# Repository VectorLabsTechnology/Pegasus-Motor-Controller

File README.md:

# Pegasus Motor Controller

## Objetivo

O objetivo do projeto é desenvolver um inversor para um motor síncrono de ímãs permanentes utilizando a técnica de controle orientado a campo. Com isso, se espera obter a familiaridadee com tecnologias modernas de controle de motores, tendo como objetivo final desenvolver um inversor capaz de acionar motores trifásicos e BLDC.

## Especificações

Em primeira instância, o motor a ser acionado será um motor oriundo de um _hoverboard_, brushless sensorado, operando a 48V e com potência máxima de 2,2kW. Com base nesses aprendizados, espera-se no futuro ser possível acionarmos um motor de maior tensão e potência, já de fabricação própria. As especificações técnicas mais específicas podem ser encontradas na [CT-001](/docs/CT-001-Especificacoes-Gerais.md).

## Organização do projeto

O repositório está dividido em quatro subdiretórios, `docs`, `fw`, `hw` e `sw`, que contêm respectivamente a documentação, firmware, hardware e software do projeto.
A parte de documentação é organizada majoritariamente no formato de [CTs](/docs/README.md). O design de hardware está sendo realizado com a ferramenta KiCad.

## Renders of the borads
Power Electronics:

Control Board:

Video of the test on a 3-phase induction motor

### Licença

O projeto está licenciado sob a licença MIT. Isso quer dizer que você tem o direto de reproduzir ele, tanto o software quanto o hardware.

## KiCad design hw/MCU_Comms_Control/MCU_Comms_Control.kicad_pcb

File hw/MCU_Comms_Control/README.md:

# Placa de controle

---

---

Essa placa é responsável por realizar o acionamento e controle dos motores. Utilizando um STM32F303, ela é capaz de medir a corrente ou força eletromotriz reversa de cada fase, possibilitando a comutação das bobinas. Além disso, possui entradas para sensores Hall, permitindo o uso de motores sensorados. 

Além do acionamento do motor, a placa realiza a comunicação com o resto do carro via barramento CAN, possibilitando o ajuste remoto de torque. Também possui uma entrada para o barramento de falha do carro, que desativa automaticamente a saída em caso de pane em qualquer um dos sistemas. Entradas para termistores permitem o monitoramento contínuo da temperatura da ponte do inversor, possibilitando o desarme em caso de sobreaquecimento. O monitoramento da tensão da bateria permite que as saídas sejam desligadas em caso de sobre/subtensão.

Com fim de telemetria, a placa conta com uma memória flash de 128Mbits, que pode ser lida através de conexão USB para possibilitar a caracterização da performance do inveersor e do motor, diagnosticar panes, entre outros.

---

Esse design é hardware livre e é disponibilizado através da licença CERN-OHL-S v2 (fortemente recíproca), disponível em inglês [aqui](https://ohwr.org/cern_ohl_s_v2.txt).

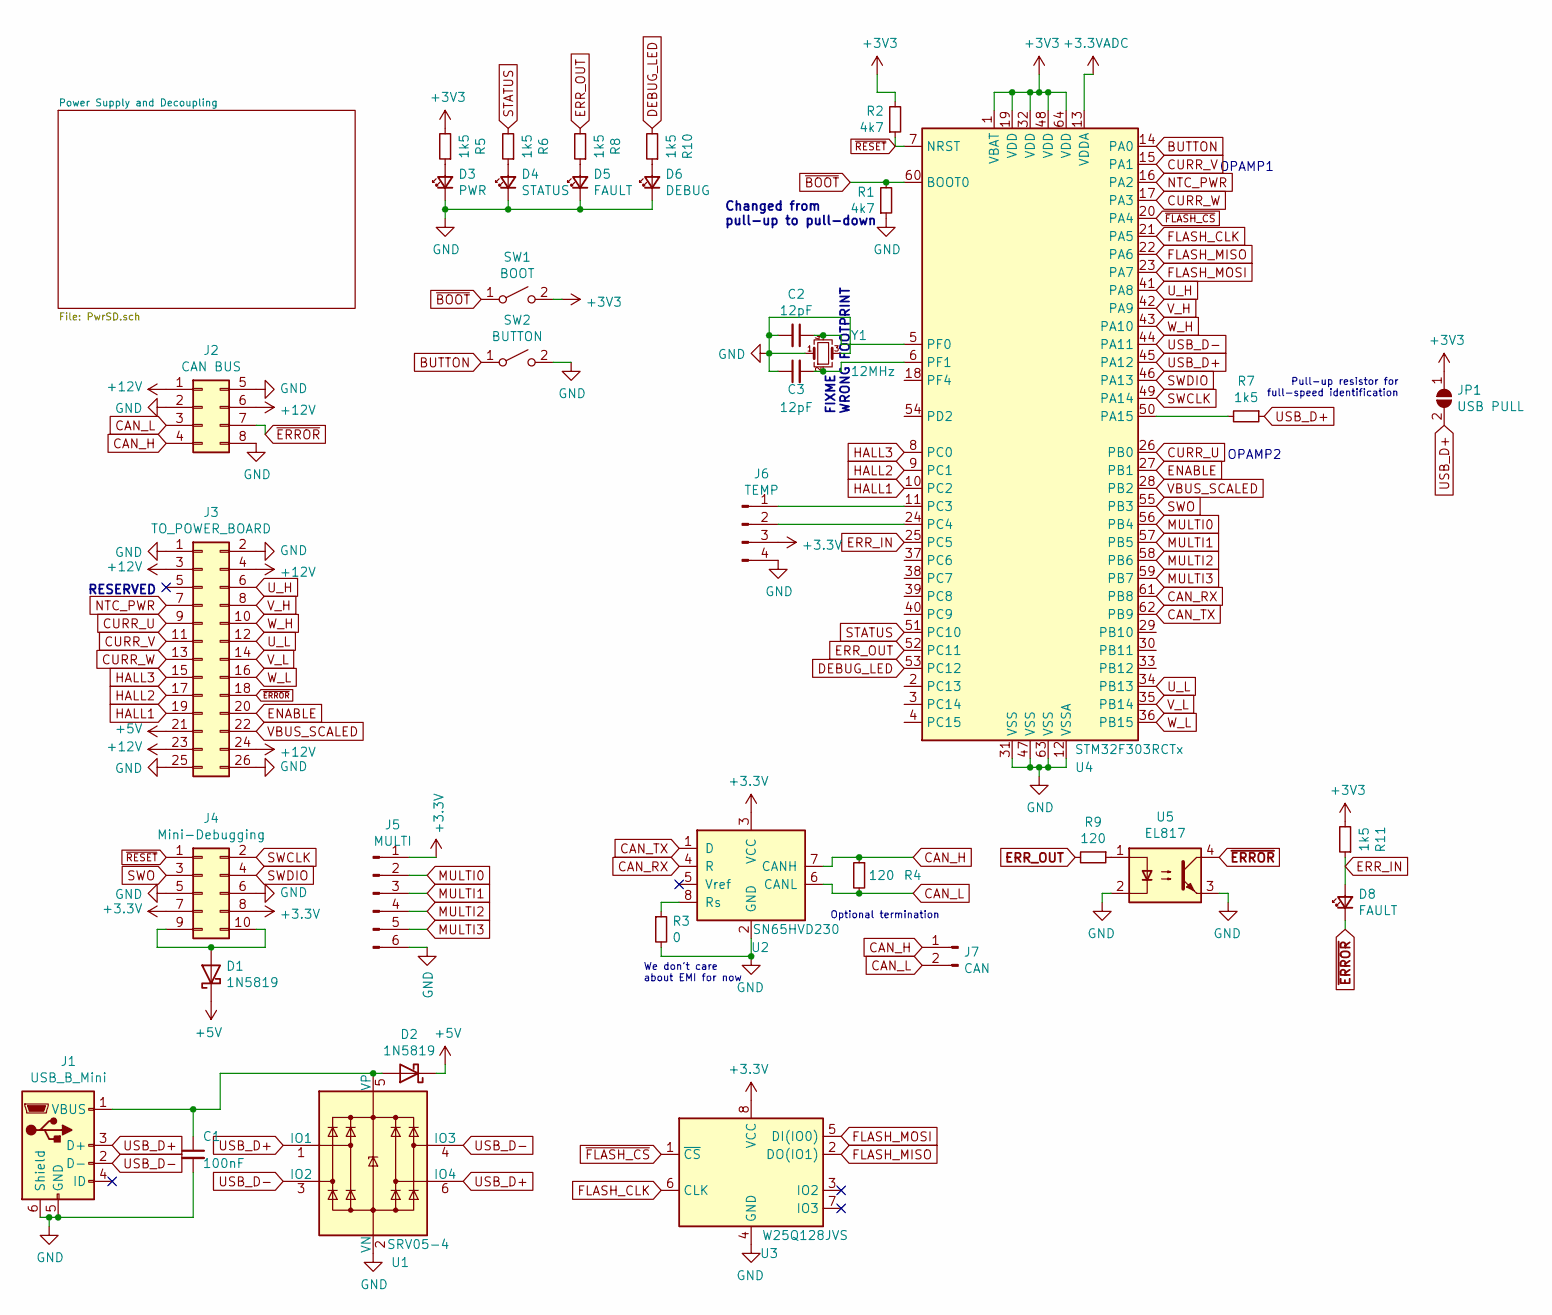
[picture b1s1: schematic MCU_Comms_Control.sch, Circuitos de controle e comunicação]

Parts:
C1: 100nF; C_0603_1608Metric; LCSC C14663
C2, C3: 12pF; C_0603_1608Metric; LCSC C38523
D1, D2: 1N5819; D_SOD-123; LCSC C8598
D3: PWR; LED_0603_1608Metric_Castellated; LCSC C72043
D4: STATUS; LED_0603_1608Metric_Castellated; LCSC C72041
D5, D8: FAULT; LED_0603_1608Metric_Castellated; LCSC C2286
D6: DEBUG; LED_0603_1608Metric_Castellated; LCSC C72041
J1: USB_B_Mini; USB_Micro-B_Molex-105133-0001
J2: CAN BUS; Molex_Mini-Fit_Jr_5566-08A_2x04_P4.20mm_Vertical
J3: TO_POWER_BOARD; IDC-Header_2x13_P2.54mm_Vertical
J4: Mini-Debugging; PinHeader_2x05_P2.54mm_Vertical
J5: MULTI; PinHeader_1x06_P2.54mm_Vertical
J6: TEMP; PinHeader_2x02_P2.54mm_Vertical
J7: CAN; PinHeader_1x02_P2.54mm_Vertical
JP1: USB PULL; SolderJumper-2_P1.3mm_Open_RoundedPad1.0x1.5mm
R1, R2: 4k7; R_0603_1608Metric; LCSC C23162
R3: 0; R_0603_1608Metric; LCSC C21189
R4, R9: 120; R_0805_2012Metric; LCSC C17437
R5, R6, R7, R8, R10, R11: 1k5; R_0603_1608Metric; LCSC C22843
SW1: BOOT; SW_SPST_PTS645
SW2: BUTTON; SW_SPST_PTS645
U1: SRV05-4; SOT-23-6; LCSC C85364
U2: SN65HVD230; SOIC-8_3.9x4.9mm_P1.27mm; LCSC C12084
U3: W25Q128JVS; SOIC-8_5.23x5.23mm_P1.27mm; LCSC C97521
U4: STM32F303RCTx; LQFP-64_10x10mm_P0.5mm
U5: EL817; SMDIP-4_W7.62mm; LCSC C106900
Y1: 12MHz; Crystal_SMD_3225-4Pin_3.2x2.5mm; LCSC C9002

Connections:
+3.3VADC: U4.13 (VDDA); also elsewhere on the board
+5V: D1.1 (K), D2.1 (K), J3.21; also elsewhere on the board
+12V: J2.1, J2.6, J3.3, J3.4, J3.23, J3.24; also elsewhere on the board
BUTTON: SW2.1 (A), U4.14 (PA0)
CAN_H: J2.4, J7.1, R4.1, U2.7 (CANH)
CAN_L: J2.3, J7.2, R4.2, U2.6 (CANL)
CAN_RX: U2.4 (R), U4.61 (PB8)
CAN_TX: U2.1 (D), U4.62 (PB9)
CURR_U: J3.9, U4.26 (PB0)
CURR_V: J3.11, U4.15 (PA1)
CURR_W: J3.13, U4.17 (PA3)
DEBUG_LED: R10.2, U4.53 (PC12)
ENABLE: J3.20, U4.27 (PB1)
ERR_IN: D8.2 (A), R11.1, U4.25 (PC5)
ERR_OUT: R8.2, R9.2, U4.52 (PC11)
FLASH_CLK: U3.6 (CLK), U4.21 (PA5)
FLASH_MISO: U3.2 (DO(IO1)), U4.22 (PA6)
FLASH_MOSI: U3.5 (DI(IO0)), U4.23 (PA7)
GND: C1.2, C2.2, C3.1, D3.1 (K), D4.1 (K), D5.1 (K), D6.1 (K), J1.5 (GND), J1.6 (Shield), J2.2, J2.5, J2.8, J3.1, J3.2, J3.25, J3.26, J4.5, J4.6, J5.6, J6.4, R1.1, R3.2, SW2.2 (B), U1.2 (VN), U2.2 (GND), U3.4 (GND), U4.12 (VSSA), U4.31 (VSS), U4.47 (VSS), U4.63 (VSS), U5.2, U5.3, Y1.1, Y1.3; also elsewhere on the board
HALL1: J3.19, U4.10 (PC2)
HALL2: J3.17, U4.9 (PC1)
HALL3: J3.15, U4.8 (PC0)
MULTI0: J5.2, U4.56 (PB4)
MULTI1: J5.3, U4.57 (PB5)
MULTI2: J5.4, U4.58 (PB6)
MULTI3: J5.5, U4.59 (PB7)
NTC_PWR: J3.7, U4.16 (PA2)
unnamed: C1.1, D2.2 (A), J1.1 (VBUS), U1.5 (VP)
unnamed: C2.1, U4.5 (PF0), Y1.4
unnamed: C3.2, U4.6 (PF1), Y1.2
unnamed: D1.2 (A), J4.9, J4.10
unnamed: D3.2 (A), R5.1
unnamed: D4.2 (A), R6.1
unnamed: D5.2 (A), R8.1
unnamed: D6.2 (A), R10.1
unnamed: J6.1, U4.11 (PC3)
unnamed: J6.2, U4.24 (PC4)
unnamed: R3.1, U2.8 (Rs)
unnamed: R7.2, U4.50 (PA15)
unnamed: R9.1, U5.1
STATUS: R6.2, U4.51 (PC10)
SWCLK: J4.2, U4.49 (PA14)
SWDIO: J4.4, U4.46 (PA13)
SWO: J4.3, U4.55 (PB3)
USB_D+: J1.3 (D+), JP1.2 (B), R7.1, U1.1 (IO1), U1.6 (IO4), U4.45 (PA12)
USB_D-: J1.2 (D-), U1.3 (IO2), U1.4 (IO3), U4.44 (PA11)
U_H: J3.6, U4.41 (PA8)
U_L: J3.12, U4.34 (PB13)
VBUS_SCALED: J3.22, U4.28 (PB2)
V_H: J3.8, U4.42 (PA9)
V_L: J3.14, U4.35 (PB14)
W_H: J3.10, U4.43 (PA10)
W_L: J3.16, U4.36 (PB15)
~BOOT: R1.2, SW1.1 (A), U4.60 (BOOT0)
~ERROR: D8.1 (K), J2.7, J3.18, U5.4
~FLASH_CS: U3.1 (~CS), U4.20 (PA4)
~RESET: J4.1, R2.1, U4.7 (NRST)

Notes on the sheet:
Optional termination
We don't care about EMI for now
Pull-up resistor for full-speed identification
RESERVED
OPAMP1
OPAMP2
Changed from pull-up to pull-down
FIXME WRONG FOOTPRINT

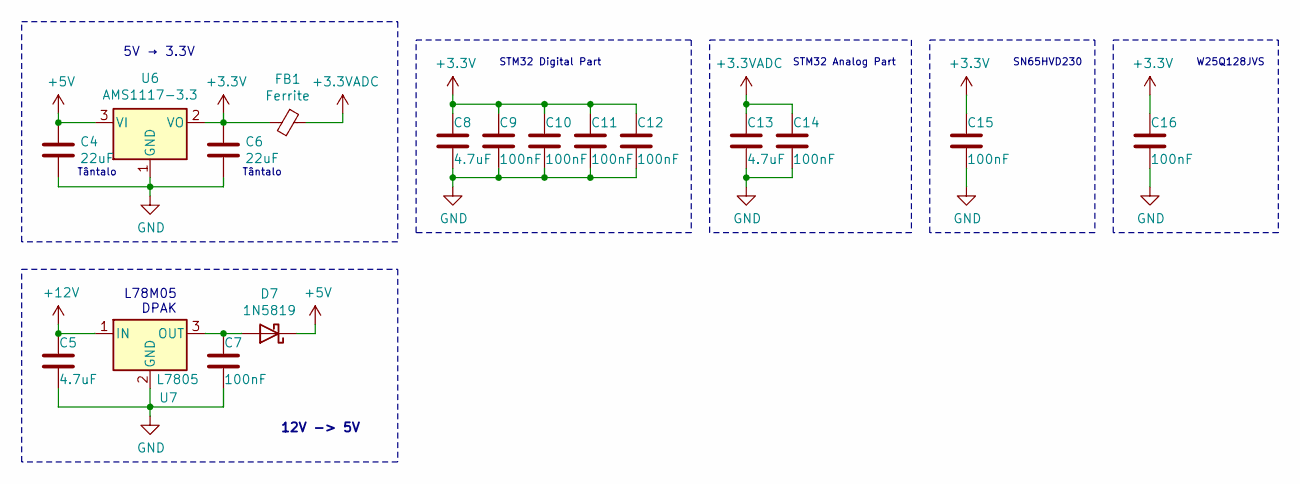
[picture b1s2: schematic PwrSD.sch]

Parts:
C4, C6: 22uF; C_0805_2012Metric; LCSC C45783
C5, C8, C13: 4.7uF; C_0603_1608Metric; LCSC C19666
C7, C9, C10, C11, C12, C14, C15, C16: 100nF; C_0603_1608Metric; LCSC C14663
D7: 1N5819; D_SOD-123; LCSC C8598
FB1: Ferrite; L_0805_2012Metric; LCSC e
U6: AMS1117-3.3; SOT-223-3_TabPin2; LCSC C6186
U7: L7805; TO-252-3_TabPin2; LCSC C58069

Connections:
+3.3VADC: C13.1, C14.1, FB1.1; also elsewhere on the board
+5V: C4.1, D7.1 (K), U6.3 (VI); also elsewhere on the board
+12V: C5.1, U7.1 (IN); also elsewhere on the board
GND: C4.2, C5.2, C6.2, C7.2, C8.2, C9.2, C10.2, C11.2, C12.2, C13.2, C14.2, C15.2, C16.2, U6.1 (GND), U7.2 (GND); also elsewhere on the board
unnamed: C7.1, D7.2 (A), U7.3 (OUT)

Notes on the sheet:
Tântalo
STM32 Digital Part
STM32 Analog Part
5V → 3.3V
SN65HVD230
W25Q128JVS
L78M05 DPAK
12V -> 5V

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
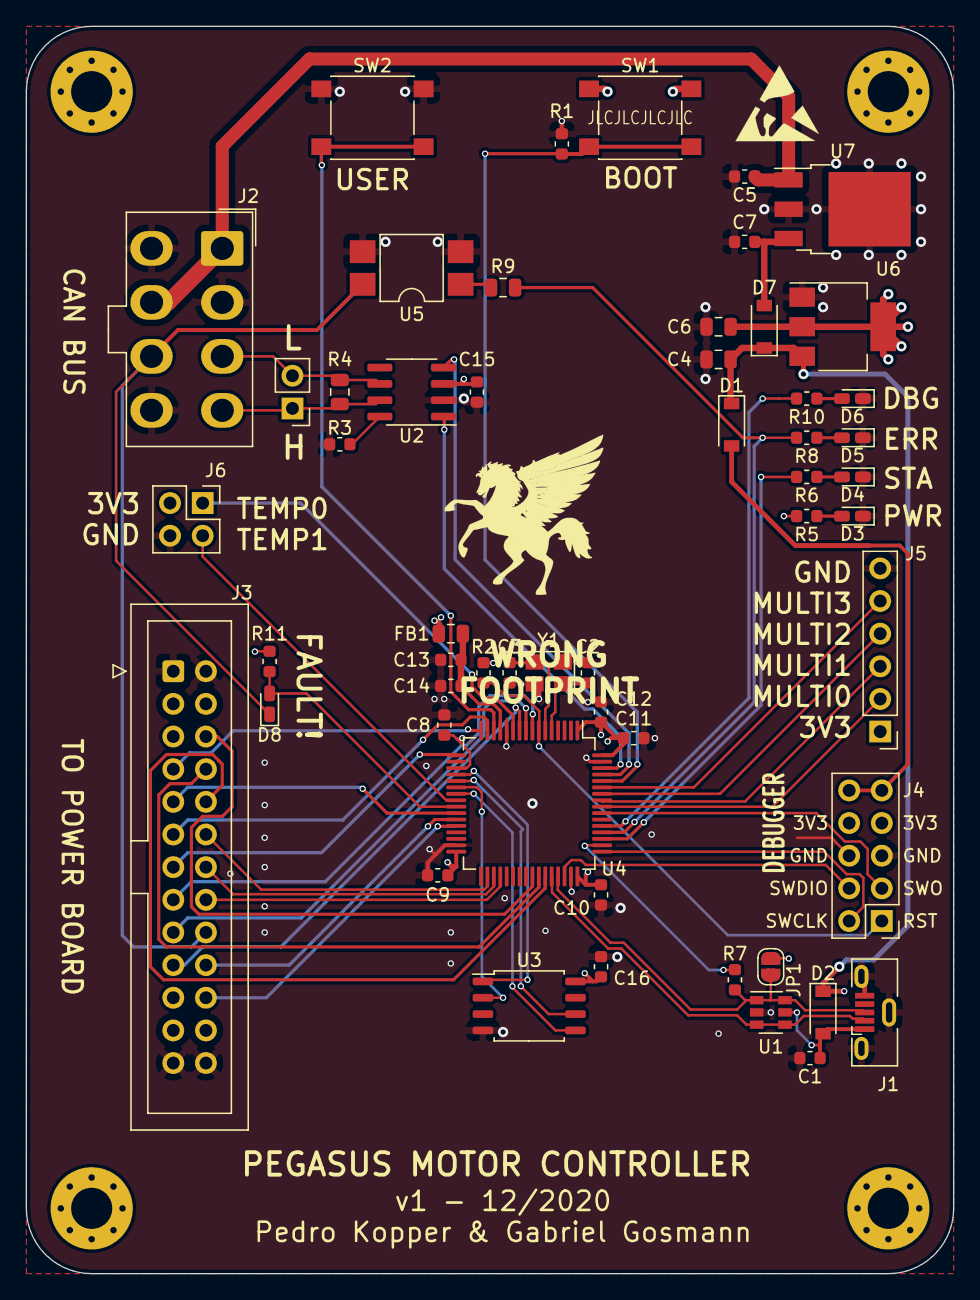
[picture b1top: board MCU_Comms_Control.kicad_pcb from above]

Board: 4 copper layers, 72.1 x 97.0 mm, 54 parts (0 on the bottom side), 59 nets.

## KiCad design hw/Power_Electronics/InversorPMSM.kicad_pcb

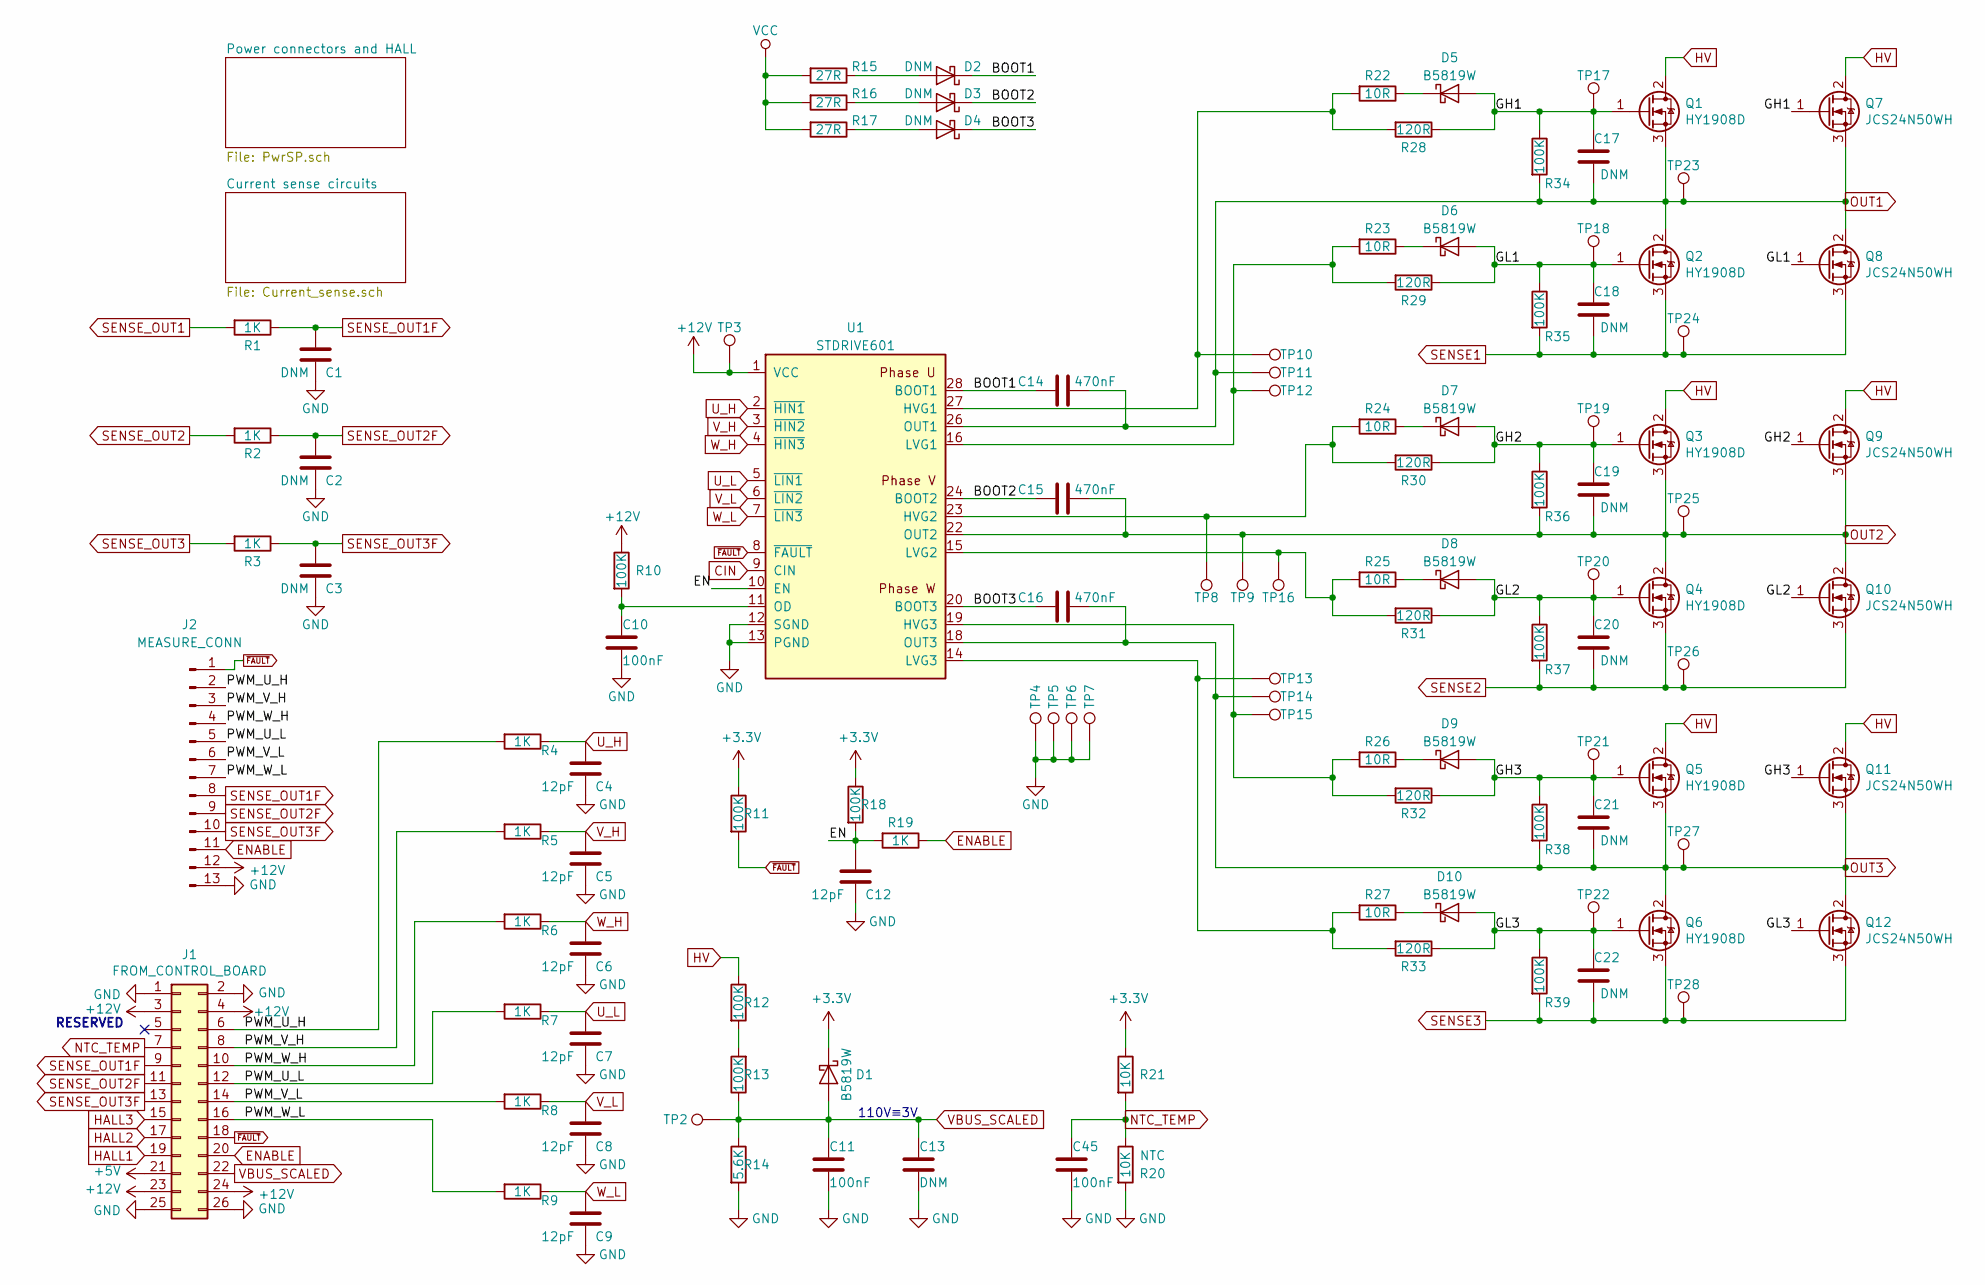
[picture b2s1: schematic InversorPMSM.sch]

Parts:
C1, C2, C3, C13, C17, C18, C19, C20, C21, C22: DNM; C_0603_1608Metric
C4, C5, C6, C7, C8, C9, C12: 12pF; C_0603_1608Metric; LCSC C38523
C10, C11, C45: 100nF; C_0603_1608Metric; LCSC C14663
C14, C15, C16: 470nF; C_0603_1608Metric; LCSC C1623
D1, D5, D6, D7, D8, D9, D10: B5819W; D_SOD-123; LCSC C8598
D2, D3, D4: DNM; D_SOD-123
J1: FROM_CONTROL_BOARD; IDC-Header_2x13_P2.54mm_Vertical
J2: MEASURE_CONN; PinHeader_1x13_P2.54mm_Vertical
Q1, Q2, Q3, Q4, Q5, Q6: HY1908D; Universal_MOSFET_generic
Q7, Q8, Q9, Q10, Q11, Q12: JCS24N50WH
R1, R2, R3, R4, R5, R6, R7, R8, R9, R19: 1K; R_0603_1608Metric; LCSC C21190
R10, R11, R18, R34, R35, R36, R37, R38, R39: 100K; R_0603_1608Metric; LCSC C25803
R12, R13: 100K; R_0805_2012Metric; LCSC C17407
R14: 5.6K; R_0805_2012Metric; LCSC C4382
R15, R16, R17: 27R; R_0603_1608Metric; LCSC C25190
R20: 10K; R_0603_1608Metric; LCSC C13564
R21: 10K; R_0603_1608Metric; LCSC C25804
R22, R23, R24, R25, R26, R27: 10R; R_0603_1608Metric; LCSC C22859
R28, R29, R30, R31, R32, R33: 120R; R_0603_1608Metric; LCSC C17437
TP2, TP3, TP4, TP5, TP6, TP7, TP8, TP9, TP10, TP11, TP12, TP13, TP14, TP15, TP16, TP17, TP18, TP19, TP20, TP21, TP22, TP23, TP24, TP25, TP26, TP27, TP28: TestPoint; TestPoint_Pad_D1.5mm
U1: STDRIVE601; SOIC-28W_7.5x17.9mm_P1.27mm

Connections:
+3V3: D1.1 (K), R11.1, R18.1, R21.1; also elsewhere on the board
+5V: J1.21; also elsewhere on the board
+12V: J1.3, J1.4, J1.23, J1.24, J2.12, R10.1, TP3.1, U1.1 (VCC); also elsewhere on the board
/BOOT1: C14.1, D2.1 (K), U1.28 (BOOT1)
/BOOT2: C15.1, D3.1 (K), U1.24 (BOOT2)
/BOOT3: C16.1, D4.1 (K), U1.20 (BOOT3)
/EN: C12.1, R18.2, R19.2, U1.10 (EN)
/GH1: C17.2, D5.2 (A), Q1.1 (G), Q7.1 (G), R28.1, R34.1, TP17.1
/GH2: C19.2, D7.2 (A), Q3.1 (G), Q9.1 (G), R30.1, R36.1, TP19.1
/GH3: C21.2, D9.2 (A), Q5.1 (G), Q11.1 (G), R32.1, R38.1, TP21.1
/GL1: C18.2, D6.2 (A), Q2.1 (G), Q8.1 (G), R29.1, R35.1, TP18.1
/GL2: C20.2, D8.2 (A), Q4.1 (G), Q10.1 (G), R31.1, R37.1, TP20.1
/GL3: C22.2, D10.2 (A), Q6.1 (G), Q12.1 (G), R33.1, R39.1, TP22.1
/PWM_U_H: J1.6, J2.2, R4.2
/PWM_U_L: J1.12, J2.5, R7.2
/PWM_V_H: J1.8, J2.3, R5.2
/PWM_V_L: J1.14, J2.6, R8.2
/PWM_W_H: J1.10, J2.4, R6.2
/PWM_W_L: J1.16, J2.7, R9.2
CIN: U1.9 (CIN); also elsewhere on the board
ENABLE: J1.20, J2.11, R19.1
GND: C1.2, C2.2, C3.2, C4.2, C5.2, C6.2, C7.2, C8.2, C9.2, C10.2, C11.2, C12.2, C13.2, C45.2, J1.1, J1.2, J1.25, J1.26, J2.13, R14.2, R20.2, TP4.1, TP5.1, TP6.1, TP7.1, U1.12 (SGND), U1.13 (PGND); also elsewhere on the board
HALL1: J1.19; also elsewhere on the board
HALL2: J1.17; also elsewhere on the board
HALL3: J1.15; also elsewhere on the board
HV: Q1.2 (D), Q3.2 (D), Q5.2 (D), Q7.2 (D), Q9.2 (D), Q11.2 (D), R12.1; also elsewhere on the board
NTC_TEMP: C45.1, J1.7, R20.1, R21.2
unnamed: C10.1, R10.2, U1.11 (OD)
unnamed: D2.2 (A), R15.1
unnamed: D3.2 (A), R16.1
unnamed: D4.2 (A), R17.1
unnamed: D5.1 (K), R22.1
unnamed: D6.1 (K), R23.1
unnamed: D7.1 (K), R24.1
unnamed: D8.1 (K), R25.1
unnamed: D9.1 (K), R26.1
unnamed: D10.1 (K), R27.1
unnamed: R12.2, R13.2
unnamed: R22.2, R28.2, TP10.1, U1.27 (HVG1)
unnamed: R23.2, R29.2, TP12.1, U1.16 (LVG1)
unnamed: R24.2, R30.2, TP8.1, U1.23 (HVG2)
unnamed: R25.2, R31.2, TP16.1, U1.15 (LVG2)
unnamed: R26.2, R32.2, TP15.1, U1.19 (HVG3)
unnamed: R27.2, R33.2, TP13.1, U1.14 (LVG3)
OUT1: C14.2, C17.1, Q1.3 (S), Q2.2 (D), Q7.3 (S), Q8.2 (D), R34.2, TP11.1, TP23.1, U1.26 (OUT1); also elsewhere on the board
OUT2: C15.2, C19.1, Q3.3 (S), Q4.2 (D), Q9.3 (S), Q10.2 (D), R36.2, TP9.1, TP25.1, U1.22 (OUT2); also elsewhere on the board
OUT3: C16.2, C21.1, Q5.3 (S), Q6.2 (D), Q11.3 (S), Q12.2 (D), R38.2, TP14.1, TP27.1, U1.18 (OUT3); also elsewhere on the board
SENSE1: C18.1, Q2.3 (S), Q8.3 (S), R35.2, TP24.1; also elsewhere on the board
SENSE2: C20.1, Q4.3 (S), Q10.3 (S), R37.2, TP26.1; also elsewhere on the board
SENSE3: C22.1, Q6.3 (S), Q12.3 (S), R39.2, TP28.1; also elsewhere on the board
SENSE_OUT1: R1.2; also elsewhere on the board
SENSE_OUT1F: C1.1, J1.9, J2.8, R1.1
SENSE_OUT2: R2.2; also elsewhere on the board
SENSE_OUT2F: C2.1, J1.11, J2.9, R2.1
SENSE_OUT3: R3.2; also elsewhere on the board
SENSE_OUT3F: C3.1, J1.13, J2.10, R3.1
U_H: C4.1, R4.1, U1.2 (~HIN1)
U_L: C7.1, R7.1, U1.5 (~LIN1)
VBUS_SCALED: C11.1, C13.1, D1.2 (A), J1.22, R13.1, R14.1, TP2.1
VCC: R15.2, R16.2, R17.2
V_H: C5.1, R5.1, U1.3 (~HIN2)
V_L: C8.1, R8.1, U1.6 (~LIN2)
W_H: C6.1, R6.1, U1.4 (~HIN3)
W_L: C9.1, R9.1, U1.7 (~LIN3)
~FAULT: J1.18, J2.1, R11.2, U1.8 (~FAULT)

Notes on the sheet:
RESERVED
110V≡3V

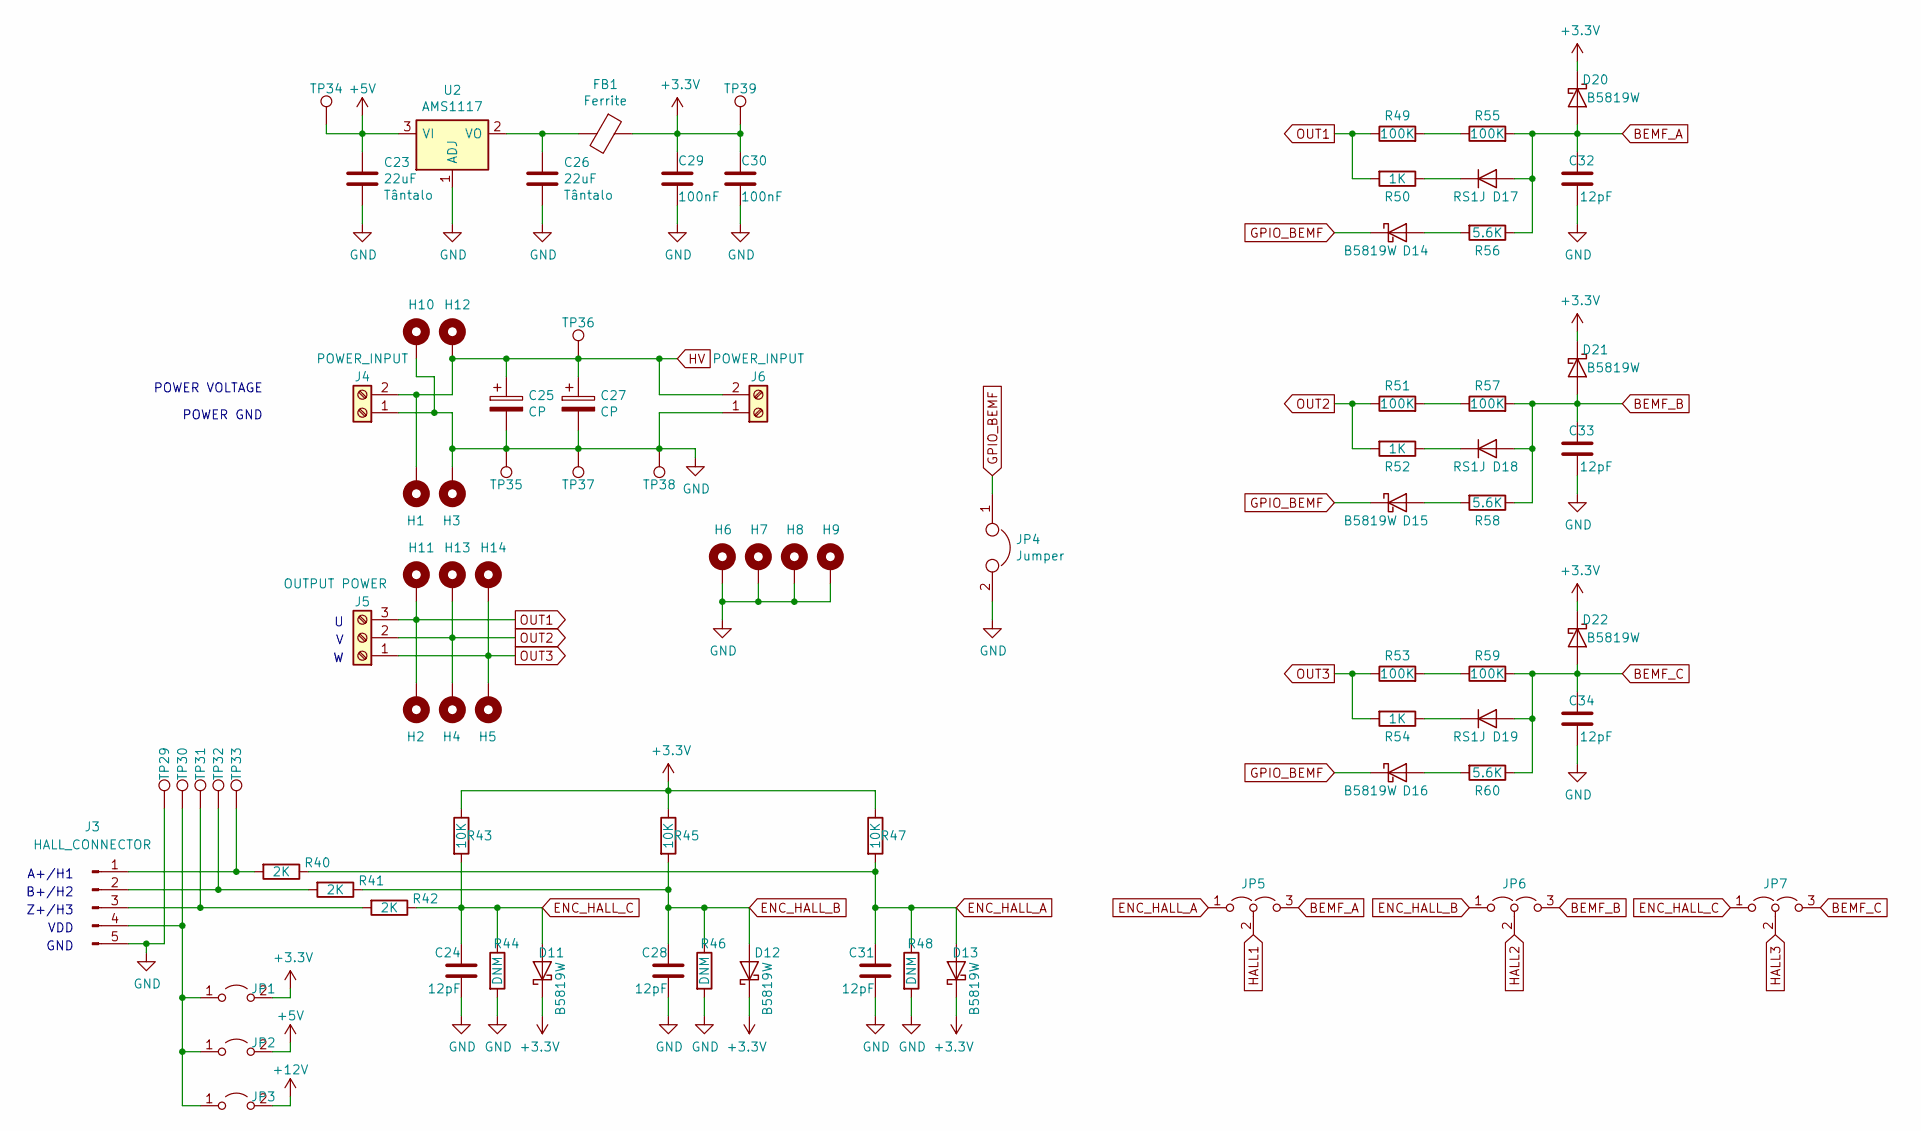
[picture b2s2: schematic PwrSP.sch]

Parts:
C23, C26: 22uF; C_0805_2012Metric; LCSC C45783
C24, C28, C31, C32, C33, C34: 12pF; C_0603_1608Metric; LCSC C38523
C25, C27: CP; CP_Radial_D18.0mm_P7.50mm_universal
C29, C30: 100nF; C_0603_1608Metric; LCSC C14663
D11, D12, D13, D14, D15, D16, D20, D21, D22: B5819W; D_SOD-123; LCSC C8598
D17, D18, D19: RS1J; D_SMA_custom; LCSC C169477
FB1: Ferrite; L_0805_2012Metric; LCSC C21189
H1, H2, H3, H4, H5: MountingHole_Pad; MountingHole_3.4mm_M3_Pad_Via
H6, H7, H8, H9: MountingHole_Pad; MountingHole_3.2mm_M3_Pad_Via
H10, H11, H12, H13, H14: MountingHole_Pad; MountingHole_2.2mm_M2_DIN965_Pad
J3: HALL_CONNECTOR; PinHeader_1x05_P2.54mm_Vertical
J4: POWER_INPUT
J5: OUTPUT POWER
J6: POWER_INPUT; Amass_XT60PW-M_Kombifootprint
JP1, JP2, JP3: Jumper_2_Open; SolderJumper-2_P1.3mm_Open_TrianglePad1.0x1.5mm
JP4: Jumper; SolderJumper-2_P1.3mm_Open_TrianglePad1.0x1.5mm
JP5, JP6, JP7: Jumper_3_Open; SolderJumper-3_P2.0mm_Open_TrianglePad1.0x1.5mm_custom
R40, R41, R42: 2K; R_0603_1608Metric; LCSC C22975
R43, R45, R47: 10K; R_0603_1608Metric; LCSC C25804
R44, R46, R48: DNM; R_0603_1608Metric
R49, R51, R53, R55, R57, R59: 100K; R_0805_2012Metric; LCSC C17407
R50, R52, R54: 1K; R_0603_1608Metric; LCSC C21190
R56, R58, R60: 5.6K; R_0805_2012Metric; LCSC C4382
TP29, TP30, TP31, TP32, TP33, TP34, TP35, TP36, TP37, TP38, TP39: TestPoint; TestPoint_Pad_D1.5mm
U2: AMS1117; SOT-223-3_TabPin2

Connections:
+3V3: C29.1, C30.1, D11.1 (K), D12.1 (K), D13.1 (K), D20.1 (K), D21.1 (K), D22.1 (K), FB1.1, JP1.2 (B), R43.1, R45.1, R47.1, TP39.1; also elsewhere on the board
+5V: C23.1, JP2.2 (B), TP34.1, U2.3 (VI); also elsewhere on the board
+12V: JP3.2 (B); also elsewhere on the board
BEMF_A: C32.2, D17.2 (A), D20.2 (A), JP5.3 (B), R55.2, R56.1
BEMF_B: C33.2, D18.2 (A), D21.2 (A), JP6.3 (B), R57.2, R58.1
BEMF_C: C34.2, D19.2 (A), D22.2 (A), JP7.3 (B), R59.2, R60.1
ENC_HALL_A: C31.2, D13.2 (A), JP5.1 (A), R40.1, R47.2, R48.1
ENC_HALL_B: C28.2, D12.2 (A), JP6.1 (A), R41.1, R45.2, R46.1
ENC_HALL_C: C24.2, D11.2 (A), JP7.1 (A), R42.1, R43.2, R44.1
GND: C23.2, C24.1, C25.2, C26.2, C27.2, C28.1, C29.2, C30.2, C31.1, C32.1, C33.1, C34.1, H3.1, H6.1, H7.1, H8.1, H9.1, H10.1, J3.5, J4.1, J6.1, JP4.2, R44.2, R46.2, R48.2, TP29.1, TP35.1, TP37.1, TP38.1, U2.1 (ADJ); also elsewhere on the board
GPIO_BEMF: D14.1 (K), D15.1 (K), D16.1 (K), JP4.1
HALL1: JP5.2 (C); also elsewhere on the board
HALL2: JP6.2 (C); also elsewhere on the board
HALL3: JP7.2 (C); also elsewhere on the board
HV: C25.1, C27.1, H1.1, H12.1, J4.2, J6.2, TP36.1; also elsewhere on the board
unnamed: C26.1, FB1.2, U2.2 (VO)
unnamed: D14.2 (A), R56.2
unnamed: D15.2 (A), R58.2
unnamed: D16.2 (A), R60.2
unnamed: D17.1 (K), R50.1
unnamed: D18.1 (K), R52.1
unnamed: D19.1 (K), R54.1
unnamed: J3.1, R40.2, TP33.1
unnamed: J3.2, R41.2, TP32.1
unnamed: J3.3, R42.2, TP31.1
unnamed: J3.4, JP1.1 (A), JP2.1 (A), JP3.1 (A), TP30.1
unnamed: R49.2, R55.1
unnamed: R51.2, R57.1
unnamed: R53.2, R59.1
OUT1: H2.1, H11.1, J5.3, R49.1, R50.2; also elsewhere on the board
OUT2: H4.1, H13.1, J5.2, R51.1, R52.2; also elsewhere on the board
OUT3: H5.1, H14.1, J5.1, R53.1, R54.2; also elsewhere on the board

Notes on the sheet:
POWER VOLTAGE
POWER GND
A+/H1
B+/H2
Z+/H3
GND
VDD

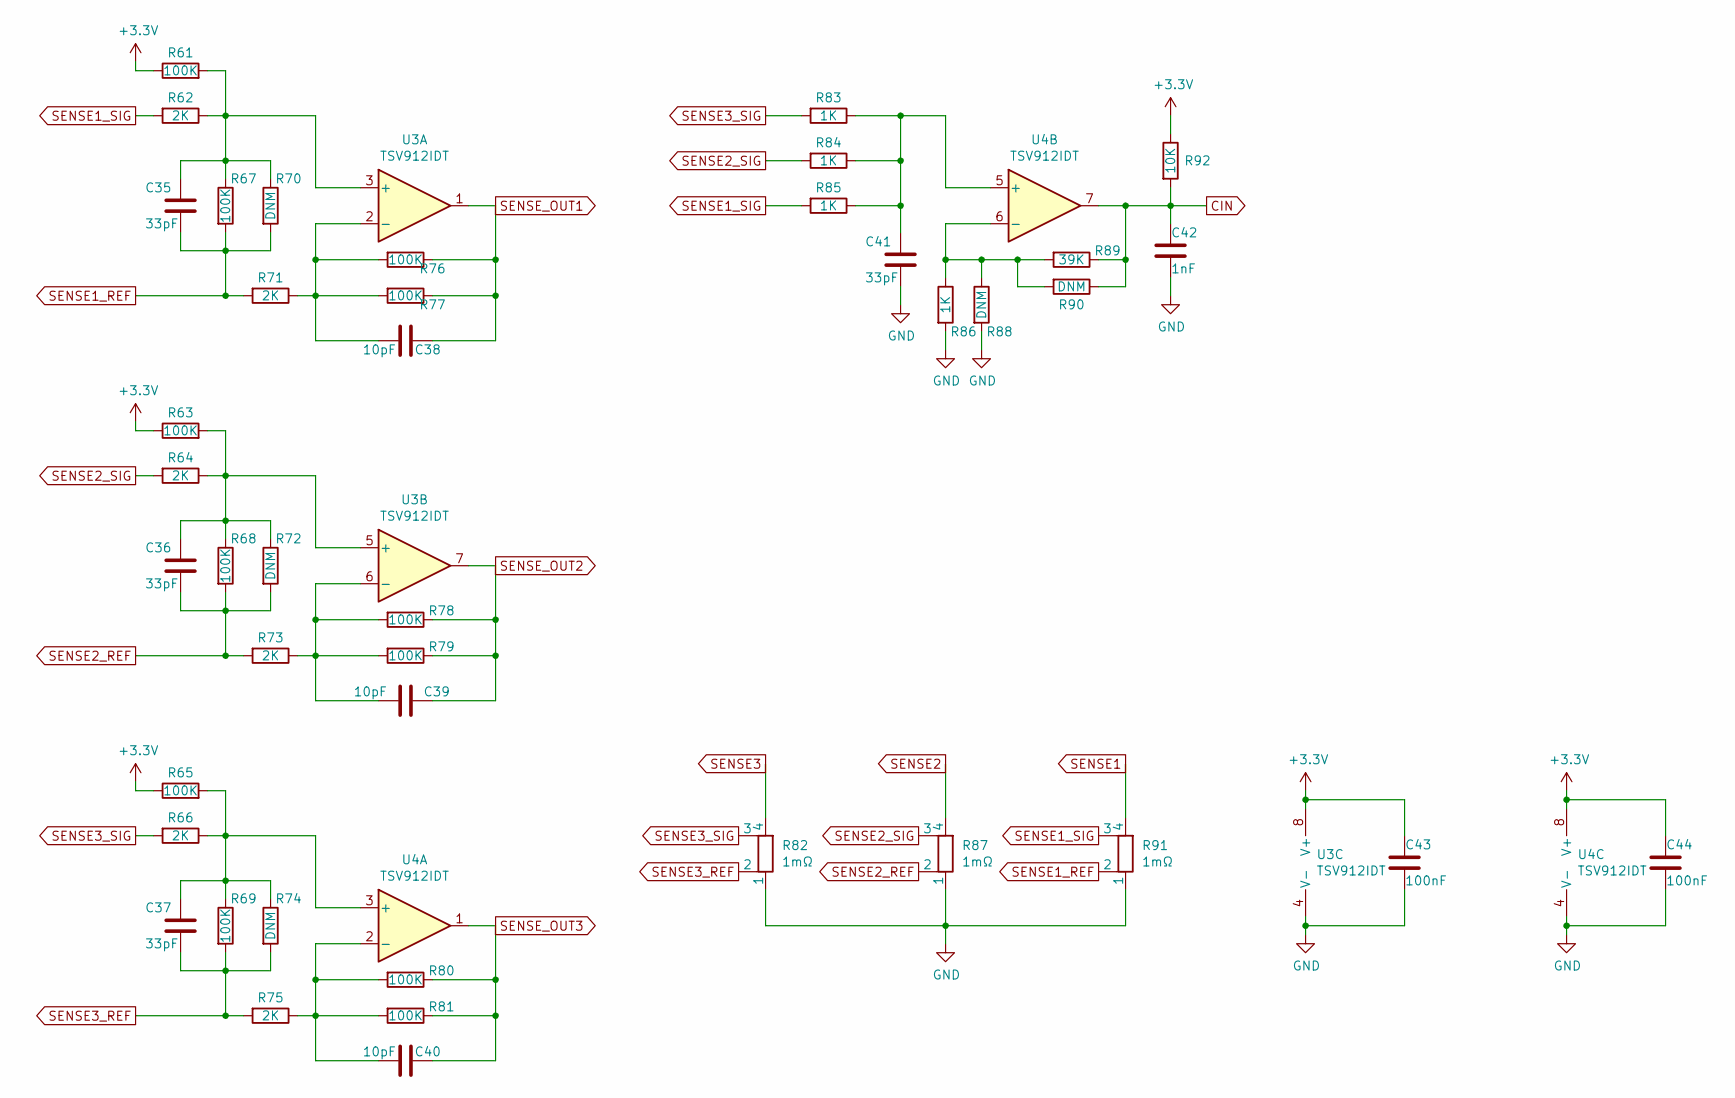
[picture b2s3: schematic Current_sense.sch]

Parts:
C35, C36, C37, C41: 33pF; C_0603_1608Metric; LCSC C1663
C38, C39, C40: 10pF; C_0603_1608Metric; LCSC C1634
C42: 1nF; C_0603_1608Metric
C43, C44: 100nF; C_0603_1608Metric; LCSC C14663
R61, R63, R65, R67, R68, R69, R76, R77, R78, R79, R80, R81: 100K; R_0603_1608Metric; LCSC C25803
R62, R64, R66, R71, R73, R75: 2K; R_0603_1608Metric; LCSC C22975
R70, R72, R74, R88, R90: DNM; R_0603_1608Metric
R82, R87, R91: 1mΩ; R_2512_6332Metric
R83, R84, R85, R86: 1K; R_0603_1608Metric; LCSC C21190
R89: 39K; R_0603_1608Metric; LCSC C23153
R92: 10K; R_0603_1608Metric; LCSC C25804
U3, U4: TSV912IDT; SOIC-8_3.9x4.9mm_P1.27mm

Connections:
+3V3: C43.1, C44.1, R61.1, R63.1, R65.1, R92.1, U3.8 (V+), U4.8 (V+); also elsewhere on the board
CIN: C42.1, R89.1, R90.1, R92.2, U4.7; also elsewhere on the board
GND: C41.2, C42.2, C43.2, C44.2, R82.1, R86.2, R87.1, R88.2, R91.1, U3.4 (V-), U4.4 (V-); also elsewhere on the board
unnamed: C35.1, R61.2, R62.1, R67.1, R70.1, U3.3 (+)
unnamed: C36.1, R63.2, R64.1, R68.1, R72.1, U3.5 (+)
unnamed: C37.1, R65.2, R66.1, R69.1, R74.1, U4.3 (+)
unnamed: C38.1, R71.1, R76.2, R77.2, U3.2 (-)
unnamed: C39.1, R73.1, R78.2, R79.2, U3.6 (-)
unnamed: C40.1, R75.1, R80.2, R81.2, U4.2 (-)
unnamed: C41.1, R83.1, R84.1, R85.1, U4.5 (+)
unnamed: R86.1, R88.1, R89.2, R90.2, U4.6 (-)
SENSE1: R91.4; also elsewhere on the board
SENSE1_REF: C35.2, R67.2, R70.2, R71.2, R91.2
SENSE1_SIG: R62.2, R85.2, R91.3
SENSE2: R87.4; also elsewhere on the board
SENSE2_REF: C36.2, R68.2, R72.2, R73.2, R87.2
SENSE2_SIG: R64.2, R84.2, R87.3
SENSE3: R82.4; also elsewhere on the board
SENSE3_REF: C37.2, R69.2, R74.2, R75.2, R82.2
SENSE3_SIG: R66.2, R82.3, R83.2
SENSE_OUT1: C38.2, R76.1, R77.1, U3.1; also elsewhere on the board
SENSE_OUT2: C39.2, R78.1, R79.1, U3.7; also elsewhere on the board
SENSE_OUT3: C40.2, R80.1, R81.1, U4.1; also elsewhere on the board

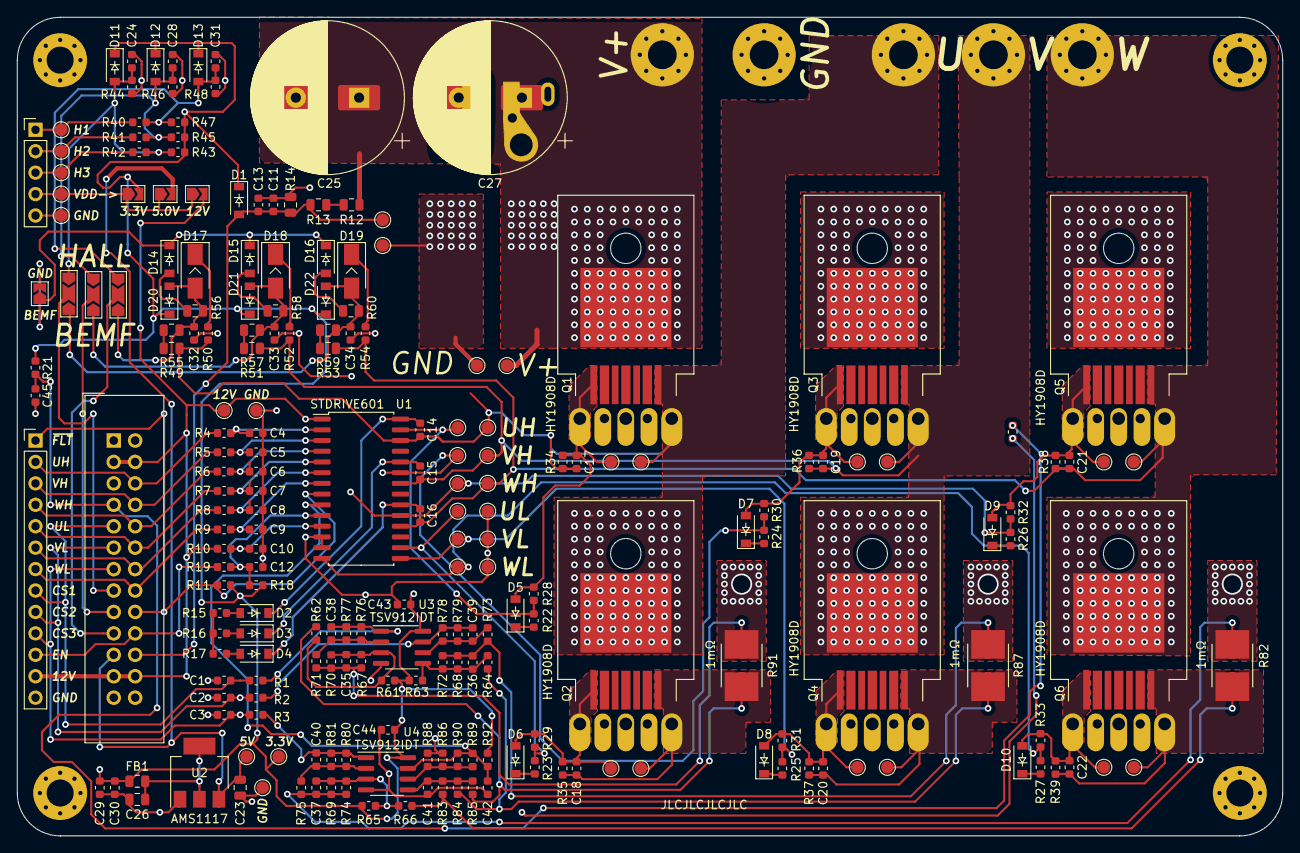
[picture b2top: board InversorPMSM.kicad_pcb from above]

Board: 2 copper layers, 150.0 x 97.0 mm, 228 parts (0 on the bottom side), 100 nets.

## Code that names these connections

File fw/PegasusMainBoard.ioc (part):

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Mcu.Name=STM32F303R(B-C)Tx
Mcu.Package=LQFP64
Mcu.UserName=STM32F303RCTx
PA0.GPIOParameters=GPIO_Label
PA0.GPIO_Label=USER_BUTTON
PA0.Signal=GPIO_Input
PA1.GPIOParameters=GPIO_Label
PA1.GPIO_Label=CURR_V
PA1.Mode=IN2-Single-Ended
PA1.Signal=ADC1_IN2
PA10.GPIOParameters=GPIO_Label
PA10.GPIO_Label=W_H
PA10.Signal=S_TIM1_CH3
PA11.Mode=Device
PA11.Signal=USB_DM
PA12.Mode=Device
PA12.Signal=USB_DP
PA13.Mode=Serial_Wire
PA13.Signal=SYS_JTMS-SWDIO
PA14.Mode=Serial_Wire
PA14.Signal=SYS_JTCK-SWCLK
PA2.GPIOParameters=GPIO_Label
PA2.GPIO_Label=NTC_PWR
PA2.Mode=IN3-Single-Ended
PA2.Signal=ADC1_IN3
PA3.GPIOParameters=GPIO_Label
PA3.GPIO_Label=CURR_W
PA3.Mode=IN4-Single-Ended
PA3.Signal=ADC1_IN4
PA4.GPIOParameters=GPIO_Label
PA4.GPIO_Label=FLASH_CS
PA4.Signal=GPIO_Output
PA5.GPIOParameters=GPIO_Label
PA5.GPIO_Label=FLASH_CLK
PA5.Mode=Full_Duplex_Master
PA5.Signal=SPI1_SCK
PA6.GPIOParameters=GPIO_Label
PA6.GPIO_Label=FLASH_MISO
PA6.Mode=Full_Duplex_Master
PA6.Signal=SPI1_MISO
PA7.GPIOParameters=GPIO_Label
PA7.GPIO_Label=FLASH_MOSI
PA7.Mode=Full_Duplex_Master
PA7.Signal=SPI1_MOSI
PA8.Mode=Clock-out
PA8.Signal=RCC_MCO
PA9.GPIOParameters=GPIO_Label
PA9.GPIO_Label=V_H
PA9.Signal=S_TIM1_CH2
PB0.GPIOParameters=GPIO_Label
PB0.GPIO_Label=CURR_U
PB0.Mode=IN12-Single-Ended
PB0.Signal=ADC3_IN12
PB1.GPIOParameters=GPIO_Label
PB1.GPIO_Label=PWR_ENABLE
PB1.Signal=GPIO_Output
PB13.GPIOParameters=GPIO_Label
PB13.GPIO_Label=U_L
PB13.Signal=TIM1_CH1N
PB14.GPIOParameters=GPIO_Label
PB14.GPIO_Label=V_L
PB14.Mode=Output Compare2 CH2 CH2N
PB14.Signal=TIM1_CH2N
PB15.GPIOParameters=GPIO_Label
PB15.GPIO_Label=W_L
PB15.Mode=Output Compare3 CH3 CH3N
PB15.Signal=TIM1_CH3N
PB2.GPIOParameters=GPIO_Label
PB2.GPIO_Label=VBUS_SCALED
PB2.Mode=IN12-Single-Ended
PB2.Signal=ADC2_IN12
PB3.Signal=SYS_JTDO-TRACESWO
PB4.GPIOParameters=GPIO_Label
PB4.GPIO_Label=MULTI0
PB4.Signal=GPIO_Input
PB5.GPIOParameters=GPIO_Label
PB5.GPIO_Label=MULTI1
PB5.Signal=GPIO_Input
PB6.GPIOParameters=GPIO_Label
PB6.GPIO_Label=MULTI2_TX
PB6.Mode=Asynchronous
PB6.Signal=USART1_TX
PB7.GPIOParameters=GPIO_Label
PB7.GPIO_Label=MULTI3_RX
PB7.Mode=Asynchronous
PB7.Signal=USART1_RX
PB8.Mode=Master
PB8.Signal=CAN_RX
PB9.Mode=Master
PB9.Signal=CAN_TX
PC0.GPIOParameters=GPIO_Label
PC0.GPIO_Label=HALL3
PC0.Signal=GPIO_Input
PC1.GPIOParameters=GPIO_Label
PC1.GPIO_Label=HALL2
PC1.Signal=GPIO_Input
PC10.GPIOParameters=GPIO_Label
PC10.GPIO_Label=STATUS
PC10.Signal=GPIO_Output
PC11.GPIOParameters=GPIO_Label
PC11.GPIO_Label=ERR_OUT
PC11.Signal=GPIO_Output
PC12.GPIOParameters=GPIO_Label
PC12.GPIO_Label=DEBUG_LED
PC12.Signal=GPIO_Output
PC2.GPIOParameters=GPIO_Label
PC2.GPIO_Label=HALL1
PC2.Signal=GPIO_Input
PC3.GPIOParameters=GPIO_Label
PC3.GPIO_Label=TEMP0
PC3.Signal=ADCx_IN9
PC4.GPIOParameters=GPIO_Label
PC4.GPIO_Label=TEMP1
PC4.Mode=IN5-Single-Ended
PC4.Signal=ADC2_IN5
PC5.GPIOParameters=GPIO_Label
PC5.GPIO_Label=ERR_IN
PC5.Mode=IN11-Single-Ended
PC5.Signal=ADC2_IN11
PF0-OSC_IN.Mode=HSE-External-Oscillator
PF0-OSC_IN.Signal=RCC_OSC_IN
PF1-OSC_OUT.Mode=HSE-External-Oscillator
PF1-OSC_OUT.Signal=RCC_OSC_OUT
RCC.HSEPLLFreq_Value=12000000
RCC.HSE_VALUE=12000000
RCC.SYSCLKFreq_VALUE=72000000
RCC.SYSCLKSourceVirtual=RCC_SYSCLKSOURCE_PLLCLK
board=custom

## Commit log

2020-11-12 estrutura basica
2020-11-14 update specifications with comments
2020-11-14 Atualizar e consolidar especificações pós reunião
2020-11-16 adicionar CT-002
2020-11-16 Start working on digital board
2020-11-18 continue digital design
2020-11-18 finish schematic of mcu/comms and start review process
2020-11-21 add footprints and lcsc code
2020-11-21 start drawing schematic
2020-11-21 finish drawing schematic and add silkscreen
2020-11-22 footprint adjust
2020-11-27 add stdrive symbol
2020-11-27 add missing files
2020-11-27 start power electronics schematic
2020-12-01 advances were made on power electronics board
2020-12-01 update schematic with hall and BEMF circuits
2020-12-02 all component's positions are more or less defined
2020-12-03 further advances made on the layout
2020-12-06 finish power board layout first pass
2020-12-06 adjustments made on silkscreen layer
2020-12-08 turn power electronics PCB into a 2 layer board
2020-12-08 remove old gerbers and assembly files
2020-12-08 new mcu board revision
2020-12-08 adjusts made on mask layer to expose high current path
2020-12-09 update pour clearences
2020-12-09 create high voltage net class and solve DRC erros
2020-12-12 change stm32 to lfqp64 (schematic)
2020-12-13 add lqfp64 board version
2020-12-13 add pegasus to new board
2020-12-14 finish new control board revision
2020-12-14 specify order number location on pcb
2020-12-14 add colateral files of new design
2020-12-14 add other colateral files of new design
2021-01-14 fix boot0 resistor
2021-01-14 start firmware development
2021-01-15 tag wrong crystal footprint
2021-05-25 mini-fit (CAN) connector hole size from 1.4 to 1.8mm diameter and add silkscreen labels for the debugger pins
2021-09-14 add power electronics renders
2021-09-14 update images

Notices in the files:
hw/MCU_Comms_Control/MCU_Comms_Control.sch:
Distribuído sob a licença CERN-OHL-S
